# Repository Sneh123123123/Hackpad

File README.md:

# Hackpad / Macropad

A compact, USB-programmable custom hackpad using the Seeed Studio XIAO MCU. This device features a 4-button layout, a rotary potentiometer, an OLED graphic display and an audio module for tactile, multimedia, and automation control.

## Hardware Specifications

- **Microcontroller:** Seeed Studio XIAO (SAMD21)
- **Components:** 
  - 4 x Buttons
  - 1 x Rotary Potentiometer 
  - 1 x Audio Module
  - 1x OLED Graphic Display

## Core Features

- **Macropad Buttons:** 4 programmable buttons mapped to keyboard shortcuts, app launches, or dev tools (or whatever you want). 
- **Rotary Potentiometer:** Rotary potentiometer for smooth scrolling, volume control, or brush resizing.
- **Audio Module:** Audio module for status chimes, error beeps, or cool sound effects.
- **Pocket-Sized:** Minimalistic layout using the ultra-small Seeed Studio XIAO footprint.
- **OLED Graphic Display:** A Graphic Display for cool illustrations, animations and displays.

## Software & Firmware Setup

### Preparation
1. Download and install the [Arduino IDE](https://arduino.cc).
2. Add Seeed Studio boards to your IDE manager using the official guide.

### Installation
1. **Clone this repository:**
   (Yet to Add)
2. **Open the project:** Launch Arduino IDE and open `...`.
3. **Select Board:** Go to Tools > Board and select your specific Seeed Studio XIAO model.
4. **Upload:** Click the upload button to flash the firmware to your hackpad.

## Pin Configuration Reference

| Component | XIAO Pin | Description |
|:----------|:---------|:------------|
| **Button 1** | D1 | (Yet to Add) |
| **Button 2** | D10 | (Yet to Add) |
| **Button 3** | D9 | (Yet to Add) |
| **Button 4** | D7 | (Yet to Add) |
| **Audio Module** | A2 (D2), A3 (D3), A8 (D8) | (Yet to Add)  |
| **Potentiometer** | D0 | (Yet to Add) |
|**OLED Graphic Display**| D4, D5| (Yet to Add)|

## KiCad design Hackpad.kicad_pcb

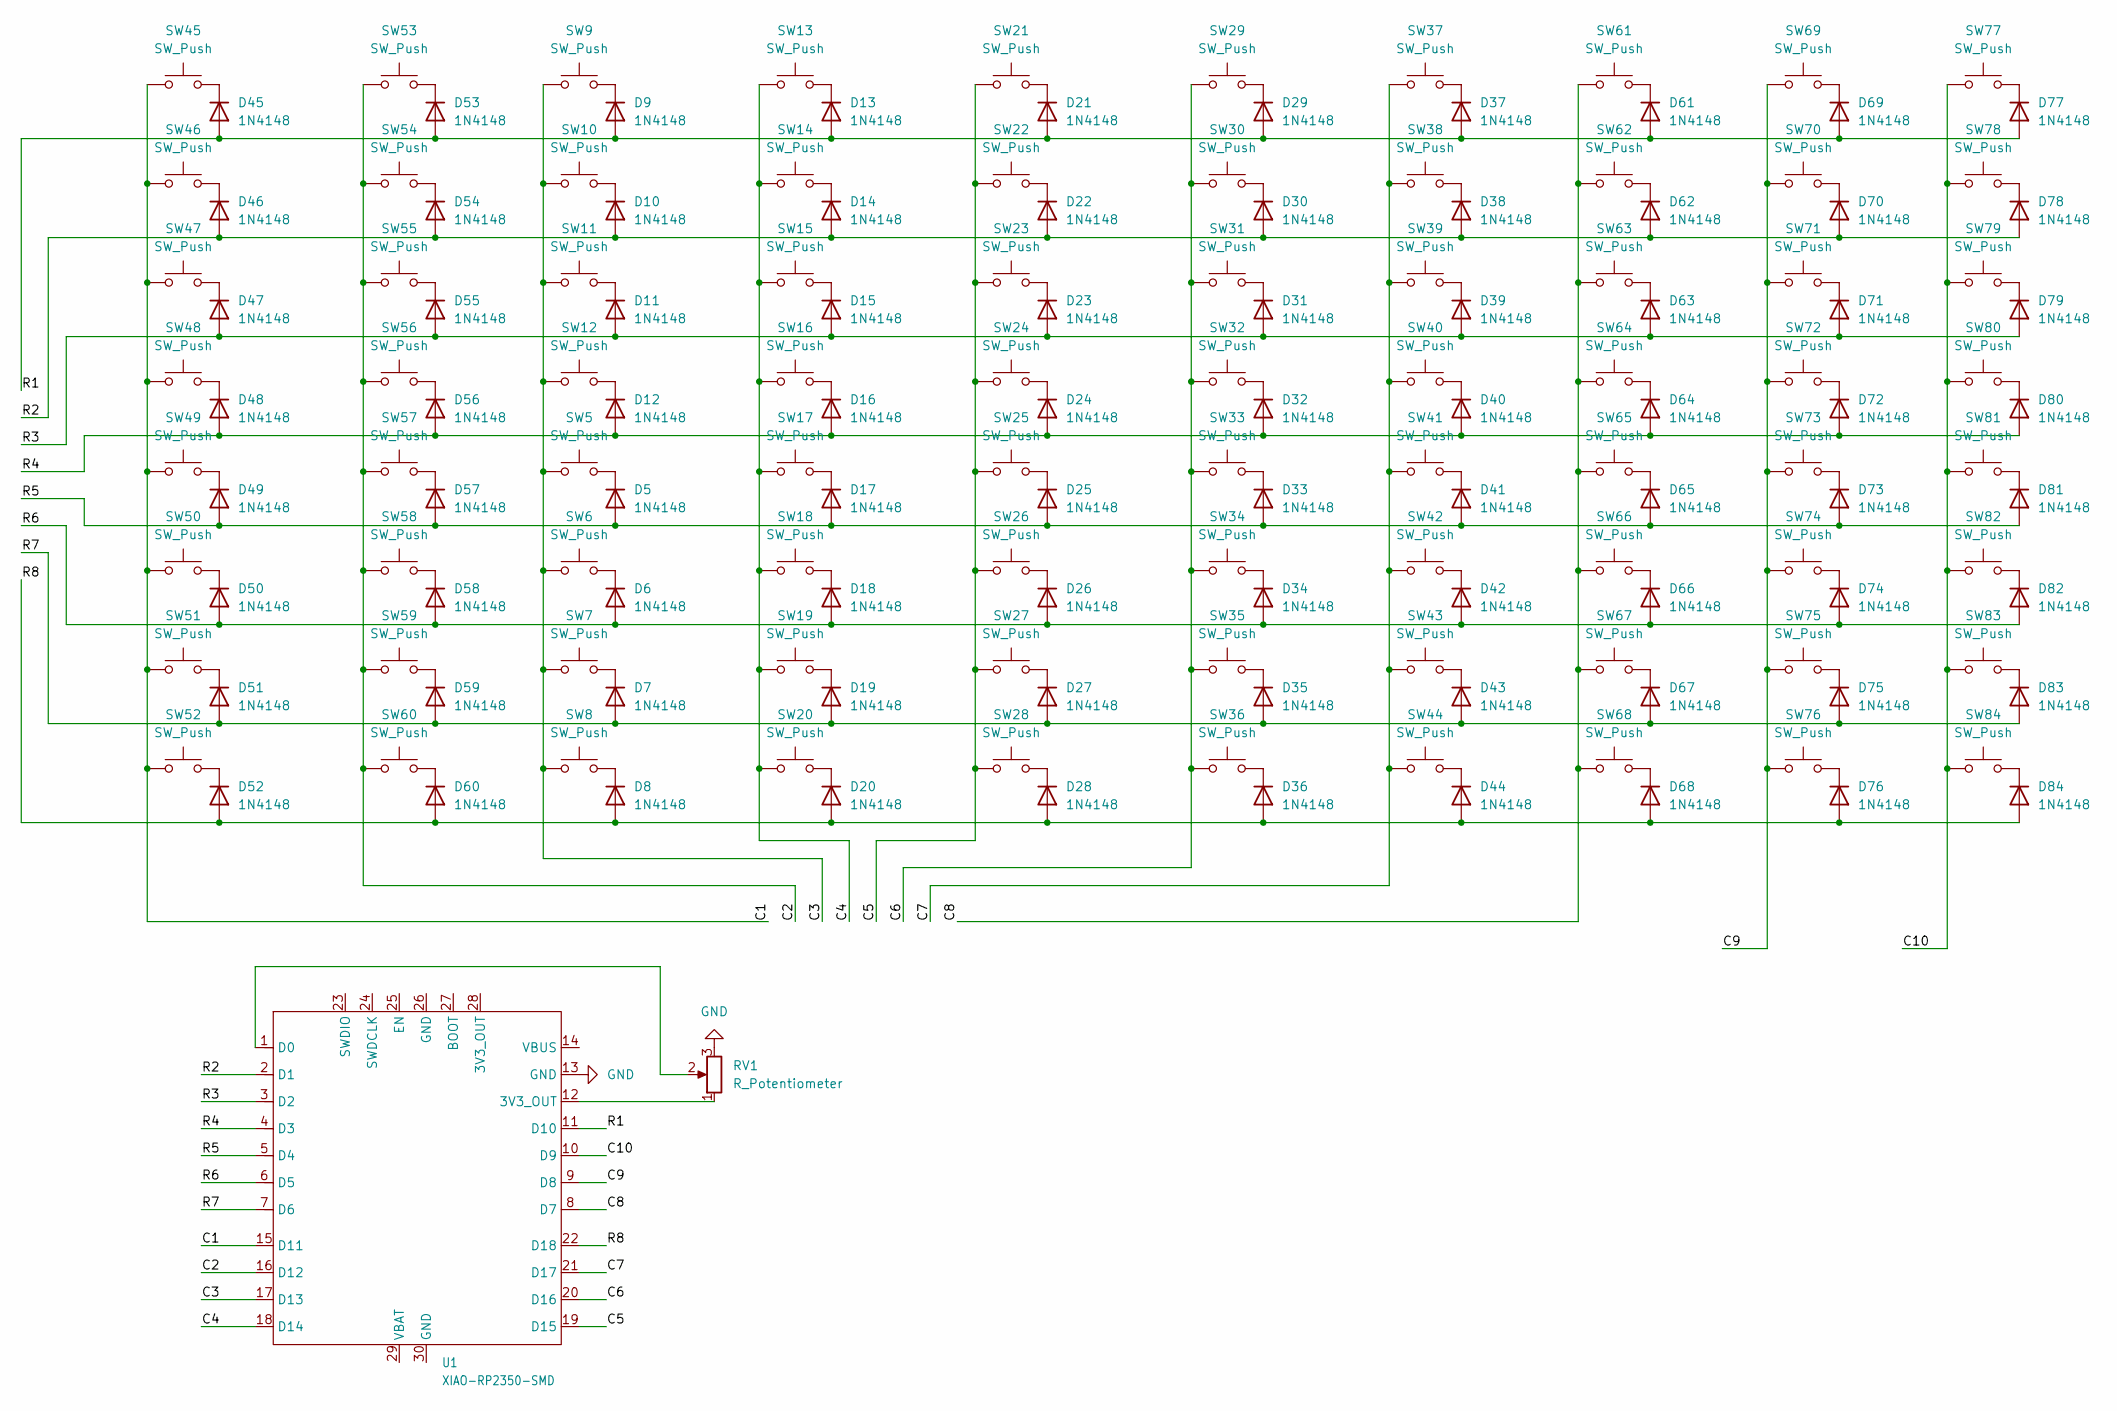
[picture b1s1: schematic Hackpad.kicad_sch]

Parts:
D5, D6, D7, D8, D9, D10, D11, D12, D13, D14, D15, D16, D17, D18, D19, D20, D21, D22, D23, D24, D25, D26, D27, D28, D29, D30, D31, D32, D33, D34, D35, D36, D37, D38, D39, D40, D41, D42, D43, D44, D45, D46, D47, D48, D49, D50, D51, D52, D53, D54, D55, D56, D57, D58, D59, D60, D61, D62, D63, D64, D65, D66, D67, D68, D69, D70, D71, D72, D73, D74, D75, D76, D77, D78, D79, D80, D81, D82, D83, D84: 1N4148; D_DO-35_SOD27_P7.62mm_Horizontal
RV1: R_Potentiometer; Potentiometer_Alps_RK09K_Single_Vertical
SW5, SW6, SW7, SW8, SW9, SW10, SW11, SW12, SW13, SW14, SW15, SW16, SW17, SW18, SW19, SW20, SW21, SW22, SW23, SW24, SW25, SW26, SW27, SW28, SW29, SW30, SW31, SW32, SW33, SW34, SW35, SW36, SW37, SW38, SW39, SW40, SW41, SW42, SW43, SW44, SW45, SW46, SW47, SW48, SW49, SW50, SW51, SW52, SW53, SW54, SW55, SW56, SW57, SW58, SW59, SW60, SW61, SW62, SW63, SW64, SW65, SW66, SW67, SW68, SW69, SW70, SW71, SW72, SW73, SW74, SW75, SW76, SW77, SW78, SW79, SW80, SW81, SW82, SW83, SW84: SW_Push; SW_Cherry_MX_1.00u_PCB
U1: XIAO-RP2350-SMD; XIAO RP2350 SMD

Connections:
/C1: SW45.1, SW46.1, SW47.1, SW48.1, SW49.1, SW50.1, SW51.1, SW52.1, U1.15 (D11)
/C2: SW53.1, SW54.1, SW55.1, SW56.1, SW57.1, SW58.1, SW59.1, SW60.1, U1.16 (D12)
/C3: SW5.1, SW6.1, SW7.1, SW8.1, SW9.1, SW10.1, SW11.1, SW12.1, U1.17 (D13)
/C4: SW13.1, SW14.1, SW15.1, SW16.1, SW17.1, SW18.1, SW19.1, SW20.1, U1.18 (D14)
/C5: SW21.1, SW22.1, SW23.1, SW24.1, SW25.1, SW26.1, SW27.1, SW28.1, U1.19 (D15)
/C6: SW29.1, SW30.1, SW31.1, SW32.1, SW33.1, SW34.1, SW35.1, SW36.1, U1.20 (D16)
/C7: SW37.1, SW38.1, SW39.1, SW40.1, SW41.1, SW42.1, SW43.1, SW44.1, U1.21 (D17)
/C8: SW61.1, SW62.1, SW63.1, SW64.1, SW65.1, SW66.1, SW67.1, SW68.1, U1.8 (D7)
/C9: SW69.1, SW70.1, SW71.1, SW72.1, SW73.1, SW74.1, SW75.1, SW76.1, U1.9 (D8)
/C10: SW77.1, SW78.1, SW79.1, SW80.1, SW81.1, SW82.1, SW83.1, SW84.1, U1.10 (D9)
/R1: D9.2 (A), D13.2 (A), D21.2 (A), D29.2 (A), D37.2 (A), D45.2 (A), D53.2 (A), D61.2 (A), D69.2 (A), D77.2 (A), U1.11 (D10)
/R2: D10.2 (A), D14.2 (A), D22.2 (A), D30.2 (A), D38.2 (A), D46.2 (A), D54.2 (A), D62.2 (A), D70.2 (A), D78.2 (A), U1.2 (D1)
/R3: D11.2 (A), D15.2 (A), D23.2 (A), D31.2 (A), D39.2 (A), D47.2 (A), D55.2 (A), D63.2 (A), D71.2 (A), D79.2 (A), U1.3 (D2)
/R4: D12.2 (A), D16.2 (A), D24.2 (A), D32.2 (A), D40.2 (A), D48.2 (A), D56.2 (A), D64.2 (A), D72.2 (A), D80.2 (A), U1.4 (D3)
/R5: D5.2 (A), D17.2 (A), D25.2 (A), D33.2 (A), D41.2 (A), D49.2 (A), D57.2 (A), D65.2 (A), D73.2 (A), D81.2 (A), U1.5 (D4)
/R6: D6.2 (A), D18.2 (A), D26.2 (A), D34.2 (A), D42.2 (A), D50.2 (A), D58.2 (A), D66.2 (A), D74.2 (A), D82.2 (A), U1.6 (D5)
/R7: D7.2 (A), D19.2 (A), D27.2 (A), D35.2 (A), D43.2 (A), D51.2 (A), D59.2 (A), D67.2 (A), D75.2 (A), D83.2 (A), U1.7 (D6)
/R8: D8.2 (A), D20.2 (A), D28.2 (A), D36.2 (A), D44.2 (A), D52.2 (A), D60.2 (A), D68.2 (A), D76.2 (A), D84.2 (A), U1.22 (D18)
GND: RV1.3, U1.13 (GND)
unnamed: D5.1 (K), SW5.2
unnamed: D6.1 (K), SW6.2
unnamed: D7.1 (K), SW7.2
unnamed: D8.1 (K), SW8.2
unnamed: D9.1 (K), SW9.2
unnamed: D10.1 (K), SW10.2
unnamed: D11.1 (K), SW11.2
unnamed: D12.1 (K), SW12.2
unnamed: D13.1 (K), SW13.2
unnamed: D14.1 (K), SW14.2
unnamed: D15.1 (K), SW15.2
unnamed: D16.1 (K), SW16.2
unnamed: D17.1 (K), SW17.2
unnamed: D18.1 (K), SW18.2
unnamed: D19.1 (K), SW19.2
unnamed: D20.1 (K), SW20.2
unnamed: D21.1 (K), SW21.2
unnamed: D22.1 (K), SW22.2
unnamed: D23.1 (K), SW23.2
unnamed: D24.1 (K), SW24.2
unnamed: D25.1 (K), SW25.2
unnamed: D26.1 (K), SW26.2
unnamed: D27.1 (K), SW27.2
unnamed: D28.1 (K), SW28.2
unnamed: D29.1 (K), SW29.2
unnamed: D30.1 (K), SW30.2
unnamed: D31.1 (K), SW31.2
unnamed: D32.1 (K), SW32.2
unnamed: D33.1 (K), SW33.2
unnamed: D34.1 (K), SW34.2
unnamed: D35.1 (K), SW35.2
unnamed: D36.1 (K), SW36.2
unnamed: D37.1 (K), SW37.2
unnamed: D38.1 (K), SW38.2
unnamed: D39.1 (K), SW39.2
unnamed: D40.1 (K), SW40.2
unnamed: D41.1 (K), SW41.2
unnamed: D42.1 (K), SW42.2
unnamed: D43.1 (K), SW43.2
unnamed: D44.1 (K), SW44.2
unnamed: D45.1 (K), SW45.2
unnamed: D46.1 (K), SW46.2
unnamed: D47.1 (K), SW47.2
unnamed: D48.1 (K), SW48.2
unnamed: D49.1 (K), SW49.2
unnamed: D50.1 (K), SW50.2
unnamed: D51.1 (K), SW51.2
unnamed: D52.1 (K), SW52.2
unnamed: D53.1 (K), SW53.2
unnamed: D54.1 (K), SW54.2
unnamed: D55.1 (K), SW55.2
unnamed: D56.1 (K), SW56.2
unnamed: D57.1 (K), SW57.2
unnamed: D58.1 (K), SW58.2
unnamed: D59.1 (K), SW59.2
unnamed: D60.1 (K), SW60.2
unnamed: D61.1 (K), SW61.2
unnamed: D62.1 (K), SW62.2
unnamed: D63.1 (K), SW63.2
unnamed: D64.1 (K), SW64.2
unnamed: D65.1 (K), SW65.2
unnamed: D66.1 (K), SW66.2
unnamed: D67.1 (K), SW67.2
unnamed: D68.1 (K), SW68.2
unnamed: D69.1 (K), SW69.2
unnamed: D70.1 (K), SW70.2
unnamed: D71.1 (K), SW71.2
unnamed: D72.1 (K), SW72.2
unnamed: D73.1 (K), SW73.2
unnamed: D74.1 (K), SW74.2
unnamed: D75.1 (K), SW75.2
unnamed: D76.1 (K), SW76.2
unnamed: D77.1 (K), SW77.2
unnamed: D78.1 (K), SW78.2
unnamed: D79.1 (K), SW79.2
unnamed: D80.1 (K), SW80.2
unnamed: D81.1 (K), SW81.2
unnamed: D82.1 (K), SW82.2
unnamed: D83.1 (K), SW83.2
unnamed: D84.1 (K), SW84.2
unnamed: RV1.1, U1.12 (3V3_OUT)
unnamed: RV1.2, U1.1 (D0)

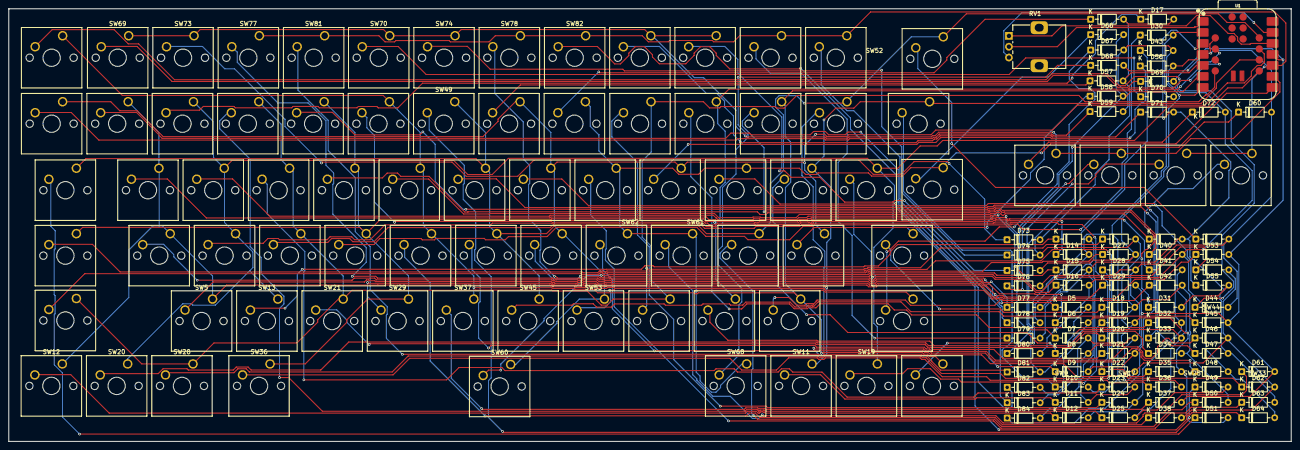
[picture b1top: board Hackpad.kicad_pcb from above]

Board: 2 copper layers, 296.3 x 100.0 mm, 162 parts (0 on the bottom side), 101 nets.

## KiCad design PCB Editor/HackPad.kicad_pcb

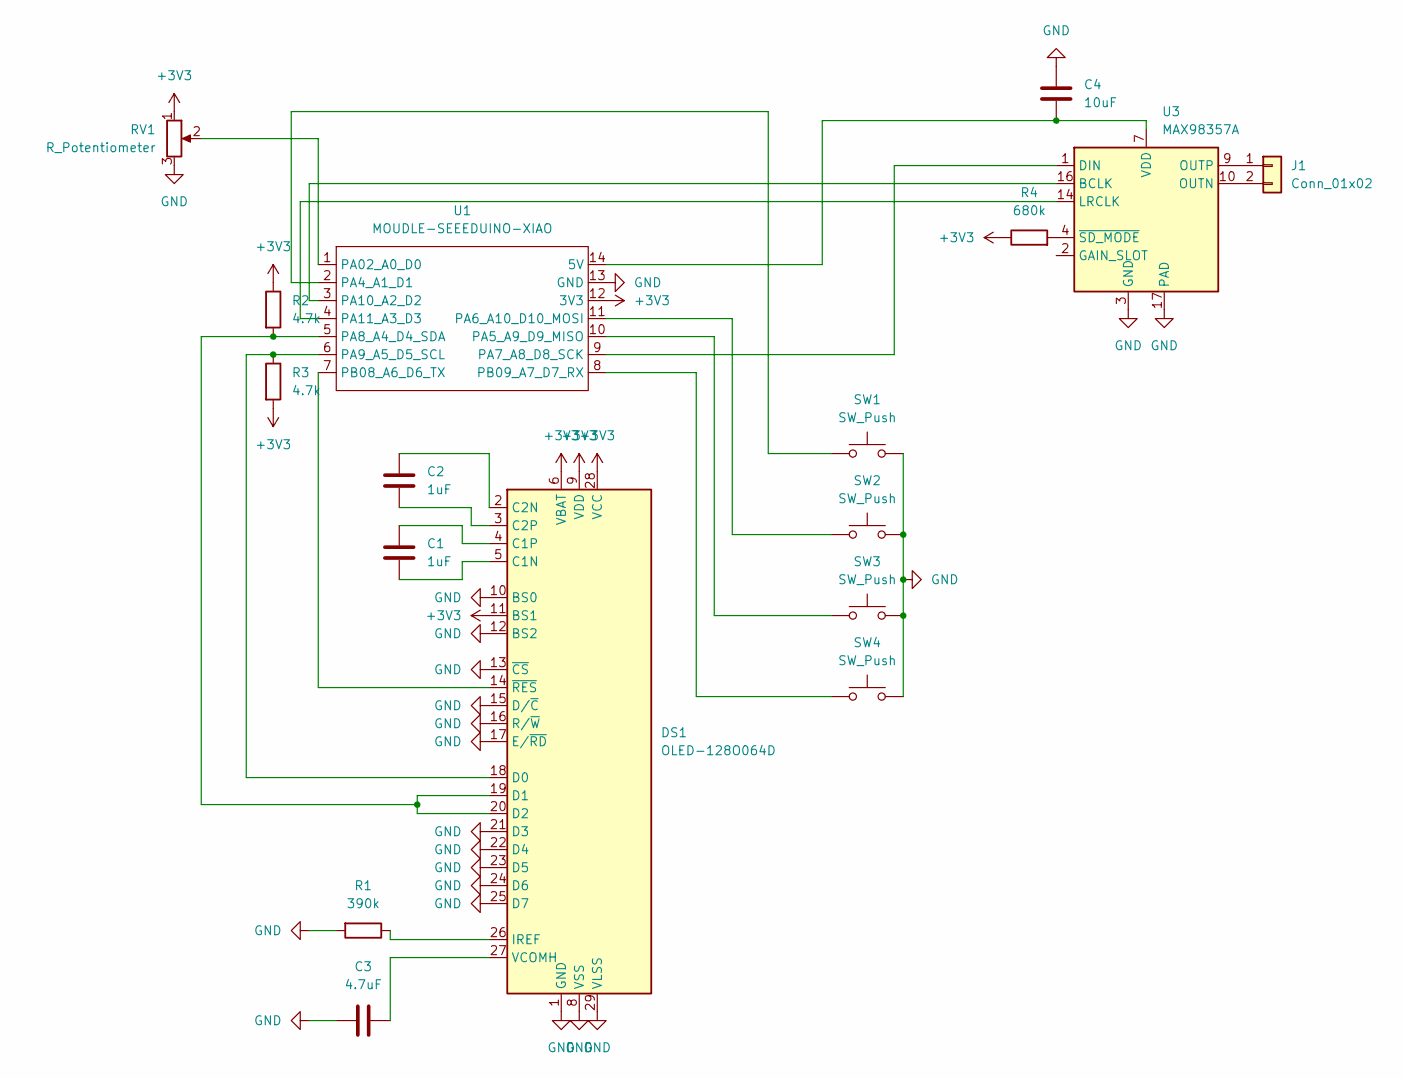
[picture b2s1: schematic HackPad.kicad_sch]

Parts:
C1, C2: 1uF; C_Disc_D5.0mm_W2.5mm_P2.50mm
C3: 4.7uF; C_Disc_D5.0mm_W2.5mm_P2.50mm
C4: 10uF; C_Disc_D5.0mm_W2.5mm_P2.50mm
DS1: OLED-128O064D
J1: Conn_01x02; PinHeader_1x02_P2.54mm_Vertical
R1: 390k; R_Axial_DIN0207_L6.3mm_D2.5mm_P7.62mm_Horizontal
R2, R3: 4.7k; R_Axial_DIN0207_L6.3mm_D2.5mm_P7.62mm_Horizontal
R4: 680k; R_Axial_DIN0207_L6.3mm_D2.5mm_P7.62mm_Horizontal
RV1: R_Potentiometer; Potentiometer_Alps_RK09K_Single_Vertical
SW1, SW2, SW3, SW4: SW_Push; SW_Cherry_MX_1.00u_PCB
U1: MOUDLE-SEEEDUINO-XIAO; XIAO-Generic-Hybrid-14P-2.54-21X17.8MM
U3: MAX98357A; QFN-16-1EP_3x3mm_P0.5mm_EP1.7x1.7mm

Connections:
+3V3: DS1.6 (VBAT), DS1.9 (VDD), DS1.11 (BS1), DS1.28 (VCC), R2.1, R3.2, R4.1, RV1.1, U1.12 (3V3)
GND: C3.2, C4.1, DS1.1 (GND), DS1.8 (VSS), DS1.10 (BS0), DS1.12 (BS2), DS1.13 (~CS), DS1.15 (D/~C), DS1.16 (R/~W), DS1.17 (E/~RD), DS1.21 (D3), DS1.22 (D4), DS1.23 (D5), DS1.24 (D6), DS1.25 (D7), DS1.29 (VLSS), DS1.30 (GND), R1.2, RV1.3, SW1.2, SW2.2, SW3.2, SW4.2, U1.13 (GND), U3.3 (GND), U3.11 (GND), U3.15 (GND), U3.17 (PAD)
unnamed: C1.2, DS1.5 (C1N)
unnamed: C1.1, DS1.4 (C1P)
unnamed: C2.1, DS1.2 (C2N)
unnamed: C2.2, DS1.3 (C2P)
unnamed: DS1.18 (D0), R3.1, U1.6 (PA9_A5_D5_SCL)
unnamed: DS1.19 (D1), DS1.20 (D2), R2.2, U1.5 (PA8_A4_D4_SDA)
unnamed: DS1.26 (IREF), R1.1
unnamed: C3.1, DS1.27 (VCOMH)
unnamed: DS1.14 (~RES), U1.7 (PB08_A6_D6_TX)
unnamed: J1.1, U3.9 (OUTP)
unnamed: J1.2, U3.10 (OUTN)
unnamed: C4.2, U1.14 (5V), U3.7 (VDD), U3.8 (VDD)
unnamed: RV1.2, U1.1 (PA02_A0_D0)
unnamed: SW1.1, U1.2 (PA4_A1_D1)
unnamed: SW3.1, U1.10 (PA5_A9_D9_MISO)
unnamed: SW2.1, U1.11 (PA6_A10_D10_MOSI)
unnamed: U1.9 (PA7_A8_D8_SCK), U3.1 (DIN)
unnamed: U1.3 (PA10_A2_D2), U3.16 (BCLK)
unnamed: U1.4 (PA11_A3_D3), U3.14 (LRCLK)
unnamed: SW4.1, U1.8 (PB09_A7_D7_RX)
unnamed: R4.2, U3.4 (~SD_MODE)

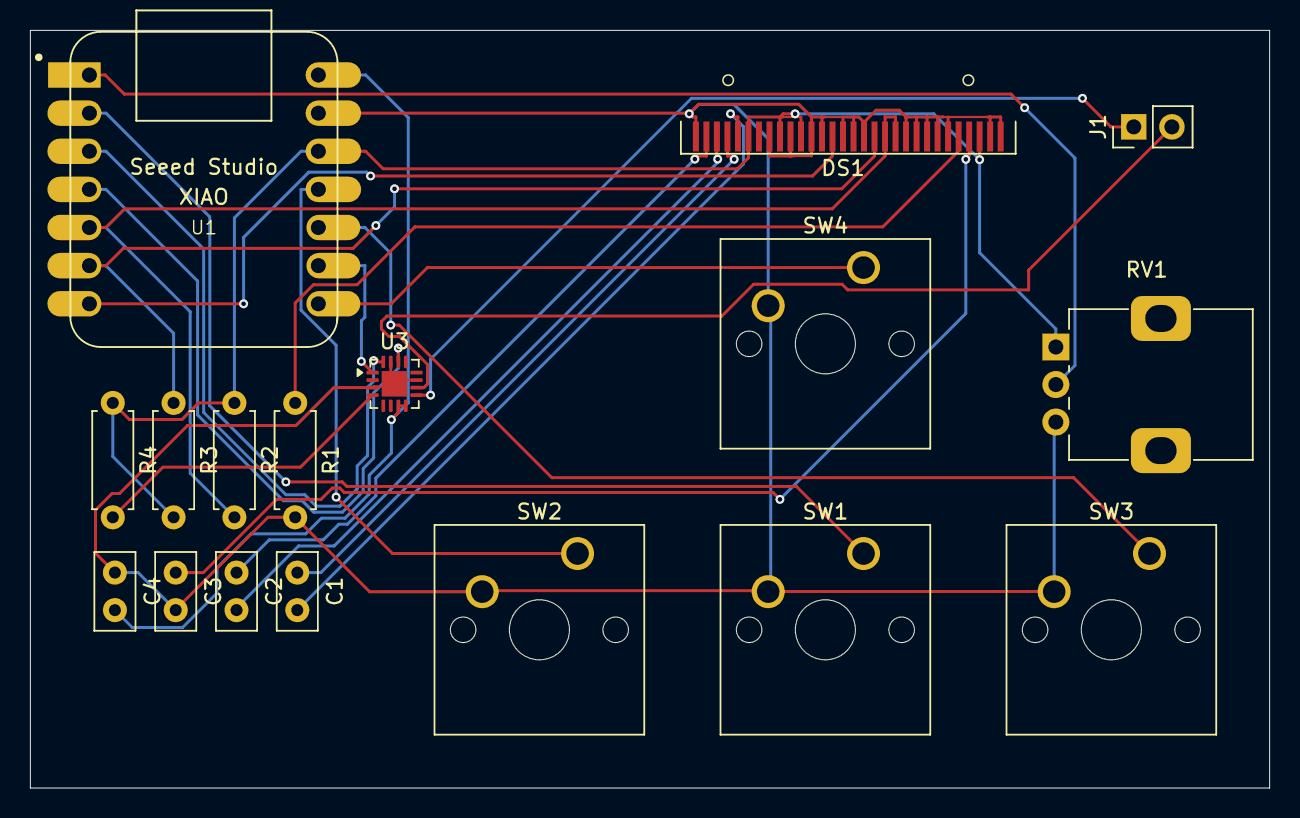
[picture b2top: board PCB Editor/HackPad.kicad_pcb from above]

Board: 2 copper layers, 82.5 x 50.5 mm, 17 parts (0 on the bottom side), 23 nets.
